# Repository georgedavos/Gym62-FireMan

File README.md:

# Gym62-FireMan
## Αυτόνομο Όχημα Ανίχνευσης Θέσης Πυρκαϊάς

Η ομάδα ρομποτικής του 62ου Γυμνασίου Αθηνών, μελετά και κατασκευάζει ένα  αυτοκινούμενο όχημα, το οποίο έχει ως σκοπό να επιτηρεί και να προστατεύει ένα δάσος από πυρκαϊά, και παράλληλα να μεταδίδει τα δεδομένα διαμέσου WiFi σημείου πρόσβασης που διαθέτει ενσωματωμένο.

Το Gym62-FireMan βασίστηκε σε ένα ερπυστριοφόρο σκάφος εκσκαφέα, το οποίο τροποποιήθηκε κατάλληλα για τις ανάγκες του έργου, ελάχιστης αξίας, και σε έναν ειδικό αισθητήρα παράταξης υπερύθρων ακτίνων. 

## Περιγραφή πλοήγησης

 Το σύστημα βασίζεται σε ένα αισθητήρα παράταξης υπέρυθρων ακτίνων.

Ο αισθητήρας παράταξης είναι δομημένος σε ένα πίνακα 8*8 στοιχείων, δίνοντας 64 ανεξάρτητα σημεία μέτρησης της θερμότητας.
 Χωρίζοντας τον αισθητήρα σε 8 ζώνες ορίζοντα, ανιχνεύεται ο ορίζοντας στον οποίο εμφανίζεται η μέγιστη θερμότητα. Με βάση τον επιλεγμένο ορίζοντα, το όχημα μεταβάλει την ταχύτητα των ερπυστριών συνεχώς, αναλογικά σε σχέση πάντα με την θέση της μέγιστης θερμότητας στον επιλεγμένο ορίζοντα.
 Αυτή ή συνεχώς μεταβαλλόμενη ταχύτητα των ερπυστριών οδηγεί με μεγάλη ακρίβεια το όχημα στην θέση της πυρκαϊάς.   
 Πιο συγκεκριμένα το όχημα περιστρέφεται συνεχώς γύρω από τον εαυτό του μετρώντας τα θερμικά φορτία του πεδίου ορατότητας. Εάν κατά την περιστροφή, μετρηθεί θερμικό φορτίο μεγαλύτερο από το προκαθορισμένο ( Triger ), τότε σταματάει και κινείται προς αυτό, διορθώνοντάς συνεχώς την πορεία του φροντίζοντας να την διατηρεί σταθερή και ευθεία μπροστά με κέντρο πάντα το μέγιστο θερμικό φορτίο, επικοινωνώντας ταυτόχρονα με το κέντρο ελέγχου μεταδίδοντας σήματα σχετικά με τις λειτουργίες του και αποδέχεται ρυθμίσεις πλοήγησης.

## Λογισμικό Κέντρου Ελέγχου.
Το Gym62RCNT είναι μια εφαρμογή τηλεμετρίας για τον έλεγχο και της ρυθμίσεις του οχήματος.
Αναπτύσσεται σε περιβάλλον NetBeans 8.6 Java JDK 1.8.
Για να τρέξετε την εφαρμογή χωρίς την χρήση Του  NetBeans. Εγκαταστήστε το  java run time environment στο συστημά σας και τρέξτε το αρχείο  Gym62RCNT.jar

## Κύκλωμα Gym62-MM3
Πρόκειται για ένα ηλεκτρονικό κύκλωμα επέκτασης οποιασδήποτε συμβατού Arduino πού λειτουργεί ως βάση σύνδεσης όλων των περιφερειακών συστημάτων τηλεμετρίας και τηλεκήνησης.
Για την ανάπτυξη του χρησιμοποιήθηκε το Ανοιχτό λογισμικό  KiCad IDE.

## Λεπτομέρεις Περιγραφές.
Περιγραφή περιεχομένων των αρχείων και των φακέλων που έχουν ενσωματωθεί στο github βρίσκεται σε αρχείο με όνομα "GYM62-FIREMAN-TreeOfFiles-Description" στον ίδιο κατάλογο με το παρόν ( https://github.com/georgedavos/Gym62-FireMan/blob/master/GYM62-FIREMAN-TreeOfFiles-Description.odt ).

Δείτε το βίντεο του έργου στο κανάλι youtube του σχολείου μας (62ο Γυμνάσιο Αθήνας)

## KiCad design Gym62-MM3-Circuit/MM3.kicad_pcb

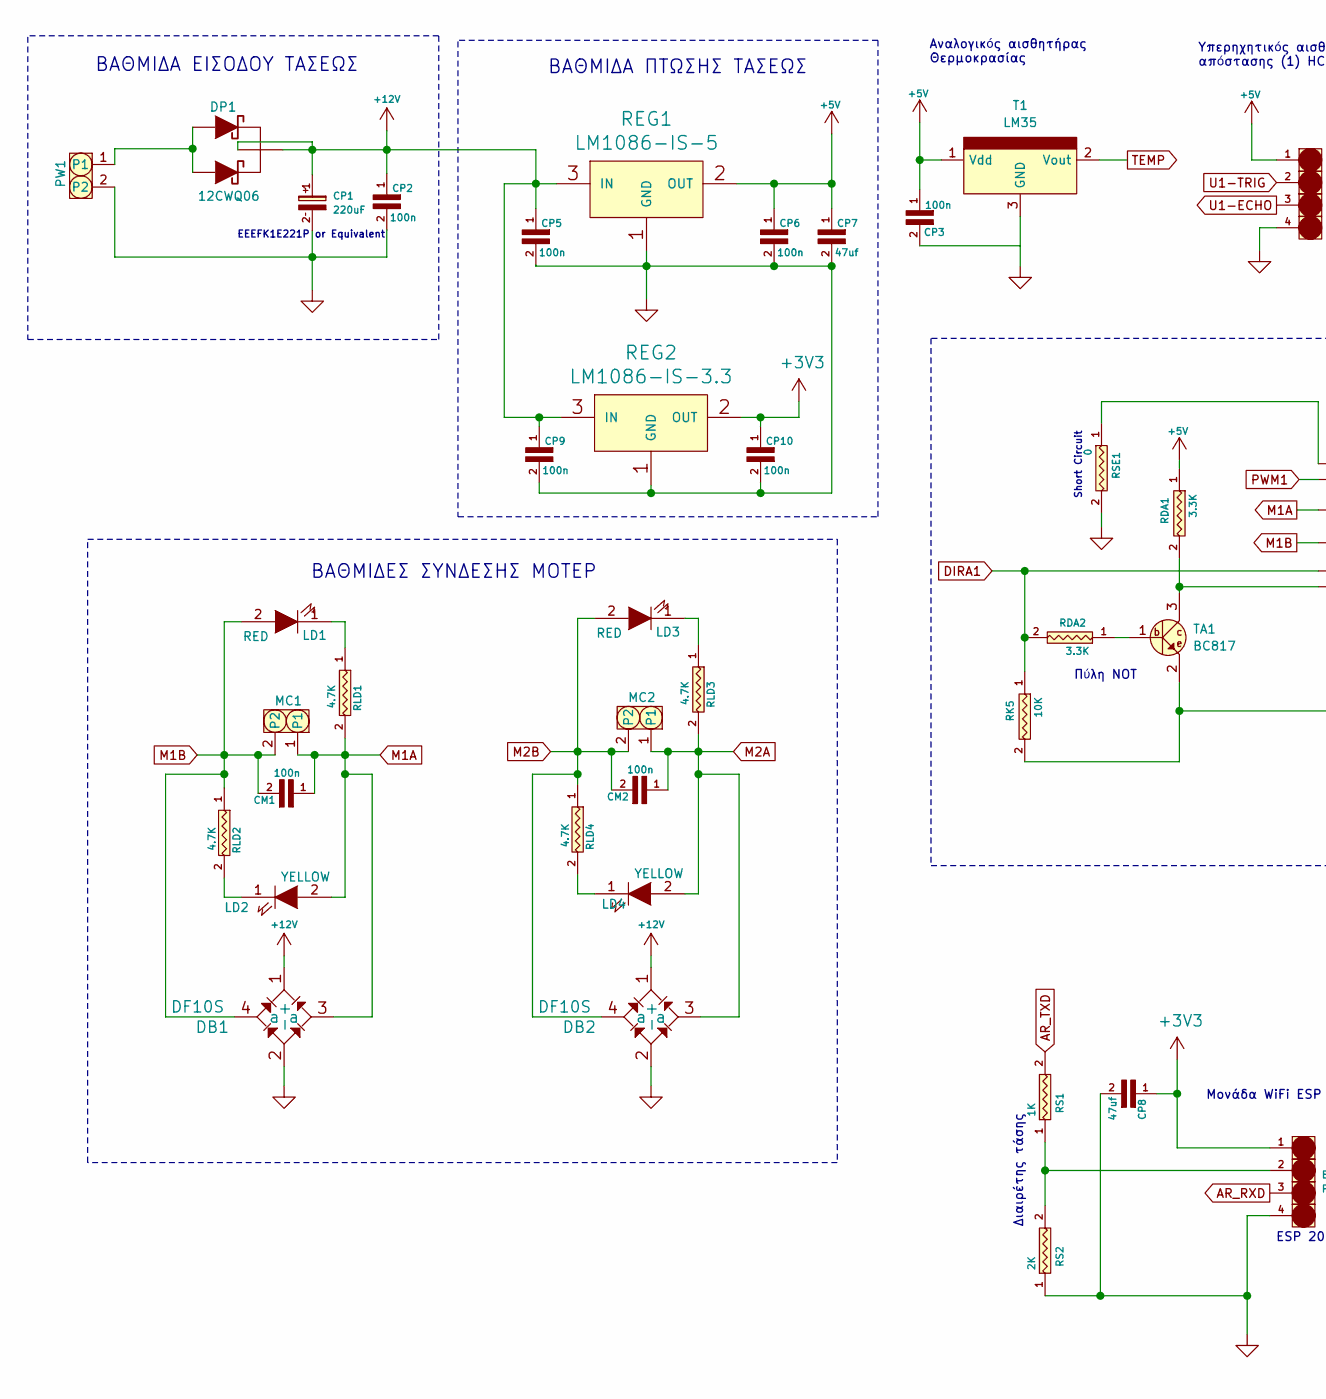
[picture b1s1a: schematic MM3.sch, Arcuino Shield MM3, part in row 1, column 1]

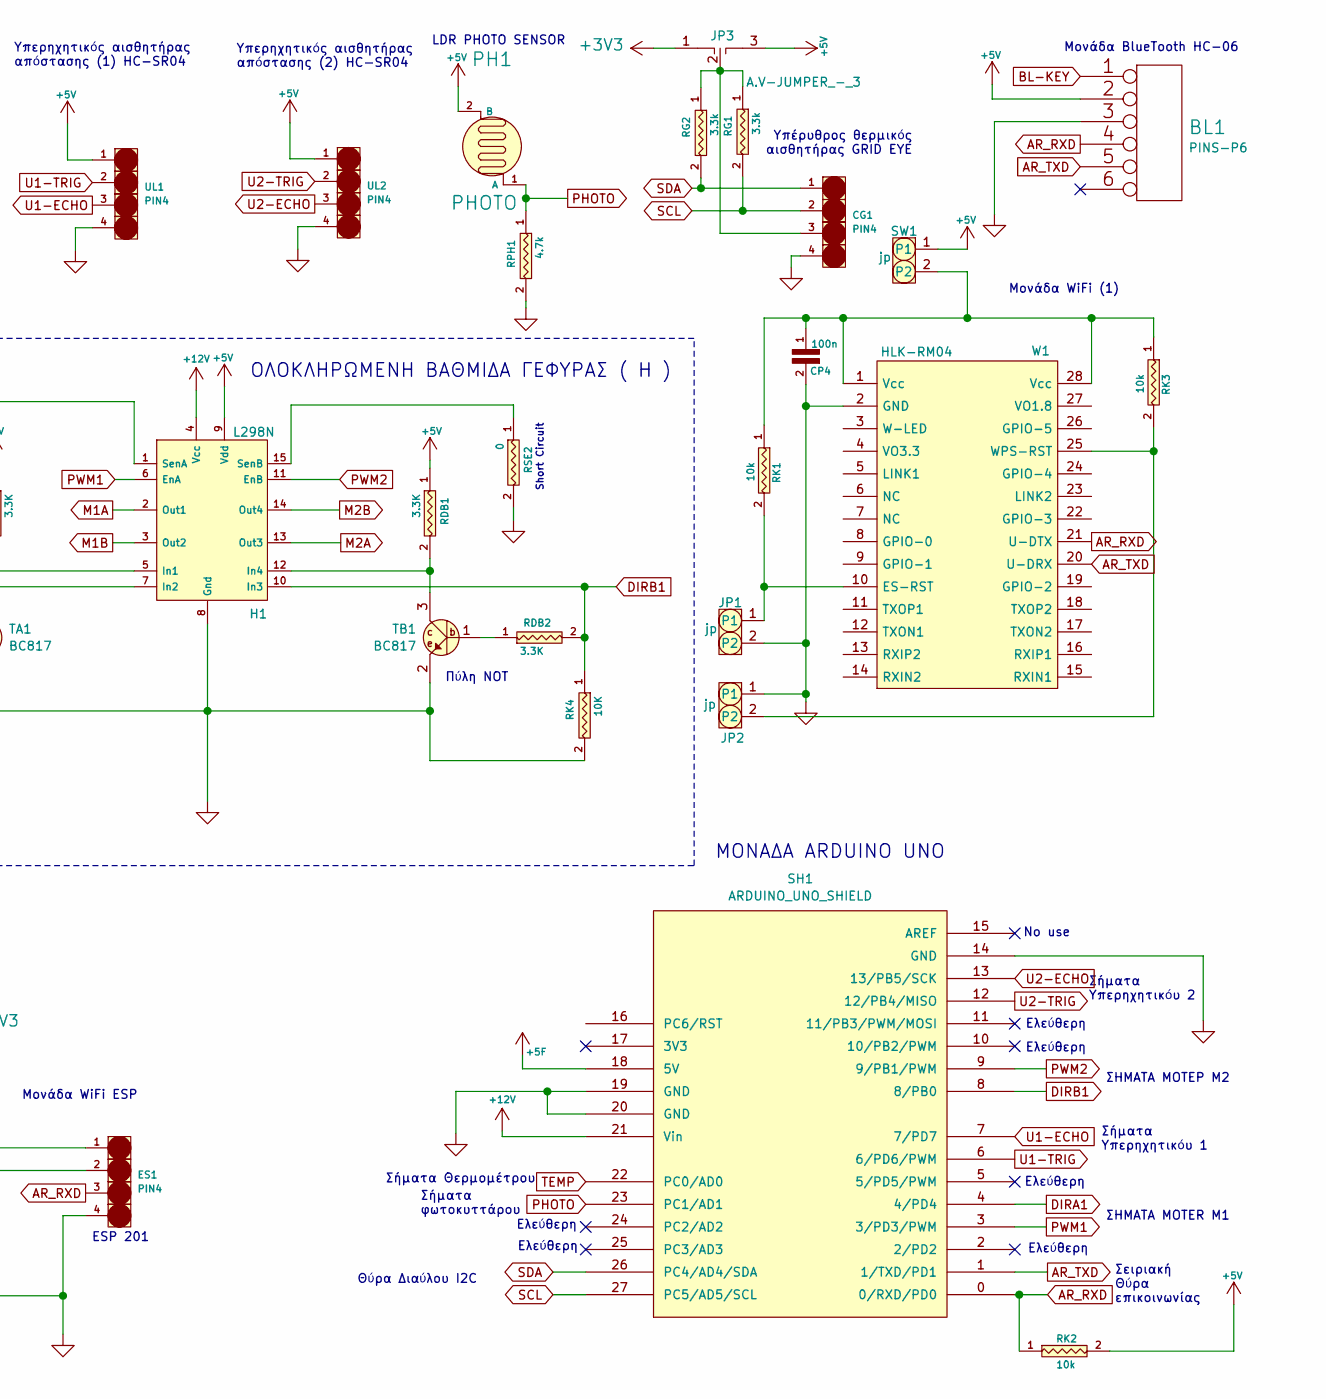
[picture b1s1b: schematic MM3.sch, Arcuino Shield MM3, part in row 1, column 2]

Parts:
BL1: PINS-P6; AV.STR-PIN-6x1
CG1: PIN4; AV.STR-MAS-4x1
CM1, CM2: 100n; AV0805
CP1: 220uF; CAP-SMD-10
CP2, CP3, CP4, CP5, CP6, CP9, CP10: 100n; AV0805
CP7, CP8: 47uf; AV1206
DB1, DB2: DF10S; Bridge-SMD
DP1: 12CWQ06; AV-D2PACK
ES1: PIN4; AV.STR-MAS-4x1
H1: L298N; Multiwat15V
JP1, JP2: jp; AV.STR-PIN-2x1
JP3: A.V-JUMPER_-_3; JP-3-MICRO
LD1, LD3: RED; PLCC2
LD2, LD4: YELLOW; PLCC2
MC1, MC2: CLEM-2P; AV.STR-MAS-2x1
PH1: PHOTO; AV.STR-MAS-2x1
PW1: CLEM-2P; AV.STR-MAS-2x1
RDA1, RDA2: 3.3K; AV1206
RDB1, RDB2: 3.3K; AV1206
REG1: LM1086-IS-5; DPAK3
REG2: LM1086-IS-3.3; DPAK3
RG1, RG2: 3.3k; AV1206
RK1, RK2, RK3: 10k; AV1206
RK4, RK5: 10K; AV1206
RLD1, RLD2, RLD3, RLD4: 4.7K; AV1206
RPH1: 4.7k; AV1206
RS1: 1K; AV1206
RS2: 2K; AV1206
RSE1, RSE2: 0; AV1206
SH1: ARDUINO_UNO_SHIELD
SW1: jp; AV.STR-PIN-2x1
T1: LM35; AV.STR-MAS-3x1
TA1: BC817; SOT23M
TB1: BC817; SOT23M
UL1, UL2: PIN4; AV.STR-PIN-4x1
W1: HLK-RM04

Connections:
+3V3: CP8.1, CP10.1, ES1.1, JP3.1, REG2.2 (OUT)
+5F: SH1.18 (5V)
+5V: BL1.2, CP3.1, CP6.1, CP7.1, H1.9 (Vdd), JP3.3, PH1.2 (B), RDA1.1, RDB1.1, REG1.2 (OUT), RK2.2, SW1.1, T1.1 (Vdd), UL1.1, UL2.1
+12V: CP1.1, CP2.1, CP5.1, CP9.1, DB1.1 (+), DB2.1 (+), DP1.2 (K), H1.4 (Vcc), REG1.3 (IN), REG2.3 (IN), SH1.21 (Vin); also elsewhere on the board
AR_RXD: BL1.4, ES1.3, RK2.1, SH1.0 (0/RXD/PD0), W1.21 (U-DTX)
AR_TXD: BL1.5, RS1.2, SH1.1 (1/TXD/PD1), W1.20 (U-DRX)
BL-KEY: BL1.1
DIRA1: H1.5 (In1), RDA2.2, RK5.1, SH1.4 (4/PD4)
DIRB1: H1.10 (In3), RDB2.2, RK4.1, SH1.8 (8/PB0)
GND: BL1.3, CG1.4, CP1.2, CP2.2, CP3.2, CP4.2, CP5.2, CP6.2, CP7.2, CP8.2, CP9.2, CP10.2, DB1.2 (-), DB2.2 (-), ES1.4, H1.8 (Gnd), JP1.2, JP2.1, PW1.2, REG1.1 (GND), REG2.1 (GND), RK4.2, RK5.2, RPH1.2, RS2.1, RSE1.2, RSE2.2, SH1.14 (GND), SH1.19 (GND), SH1.20 (GND), T1.3 (GND), TA1.2, TB1.2, UL1.4, UL2.4, W1.2 (GND); also elsewhere on the board
M1A: CM1.1, DB1.3 (a), H1.2 (Out1), LD2.2 (A), MC1.1, RLD1.2
M1B: CM1.2, DB1.4 (a), H1.3 (Out2), LD1.2 (A), MC1.2, RLD2.1
M2A: CM2.1, DB2.3 (a), H1.13 (Out3), LD4.2 (A), MC2.1, RLD3.2; also elsewhere on the board
M2B: CM2.2, DB2.4 (a), H1.14 (Out4), LD3.2 (A), MC2.2, RLD4.1; also elsewhere on the board
unnamed: CG1.3, JP3.2, RG1.1, RG2.1
unnamed: CP4.1, RK1.1, RK3.1, SW1.2, W1.1 (Vcc), W1.28 (Vcc)
unnamed: DP1.1 (A1), DP1.3 (A2), PW1.1
unnamed: ES1.2, RS1.1, RS2.2
unnamed: H1.1 (SenA), RSE1.1
unnamed: H1.7 (In2), RDA1.2, TA1.3
unnamed: H1.12 (In4), RDB1.2, TB1.3
unnamed: H1.15 (SenB), RSE2.1
unnamed: JP1.1, RK1.2, W1.10 (ES-RST)
unnamed: JP2.2, RK3.2, W1.25 (WPS-RST)
unnamed: LD1.1 (K), RLD1.1
unnamed: LD2.1 (K), RLD2.2
unnamed: LD3.1 (K), RLD3.1
unnamed: LD4.1 (K), RLD4.2
unnamed: RDA2.1, TA1.1
unnamed: RDB2.1, TB1.1
PHOTO: PH1.1 (A), RPH1.1, SH1.23 (PC1/AD1)
PWM1: H1.6 (EnA), SH1.3 (3/PD3/PWM)
PWM2: H1.11 (EnB), SH1.9 (9/PB1/PWM)
SCL: CG1.2, RG1.2, SH1.27 (PC5/AD5/SCL)
SDA: CG1.1, RG2.2, SH1.26 (PC4/AD4/SDA)
TEMP: SH1.22 (PC0/AD0), T1.2 (Vout)
U1-ECHO: SH1.7 (7/PD7), UL1.3
U1-TRIG: SH1.6 (6/PD6/PWM), UL1.2
U2-ECHO: SH1.13 (13/PB5/SCK), UL2.3
U2-TRIG: SH1.12 (12/PB4/MISO), UL2.2

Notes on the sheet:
ΣΗΜΑΤΑ MOTER M1
ΣΗΜΑΤΑ ΜΟΤΕΡ M2
Υπέρυθρος θερμικός αισθητήρας GRID EYE
Αναλογικός αισθητήρας Θερμοκρασίας
LDR PHOTO SENSOR
Σήματα Θερμομέτρου
Σήματα φωτοκυττάρου
Σήματα Υπερηχητικόυ 1
Υπερηχητικός αισθητήρας απόστασης (1) HC-SR04
Υπερηχητικός αισθητήρας απόστασης (2) HC-SR04
Σήματα Υπερηχητικόυ 2
Μονάδα WiFi (1)
Μονάδα BlueTooth HC-06
ESP 201
ΒΑΘΜΙΔΑ ΕΙΣΟΔΟΥ ΤΑΣΕΩΣ
ΒΑΘΜΙΔΑ ΠΤΩΣΗΣ ΤΑΣΕΩΣ
ΒΑΘΜΙΔΕΣ ΣΥΝΔΕΣΗΣ ΜΟΤΕΡ
ΟΛΟΚΛΗΡΩΜΕΝΗ ΒΑΘΜΙΔA ΓΕΦΥΡΑΣ ( H )
ΜΟΝΑΔΑ ARDUINO UNO
Μονάδα WiFi ESP
Σειριακή Θύρα επικοινωνίας
Ελεύθερη
No use
Θύρα Διαύλου I2C
Πύλη NOT
Διαιρέτης τάσης
EEEFK1E221P or Equivalent
Short Circuit

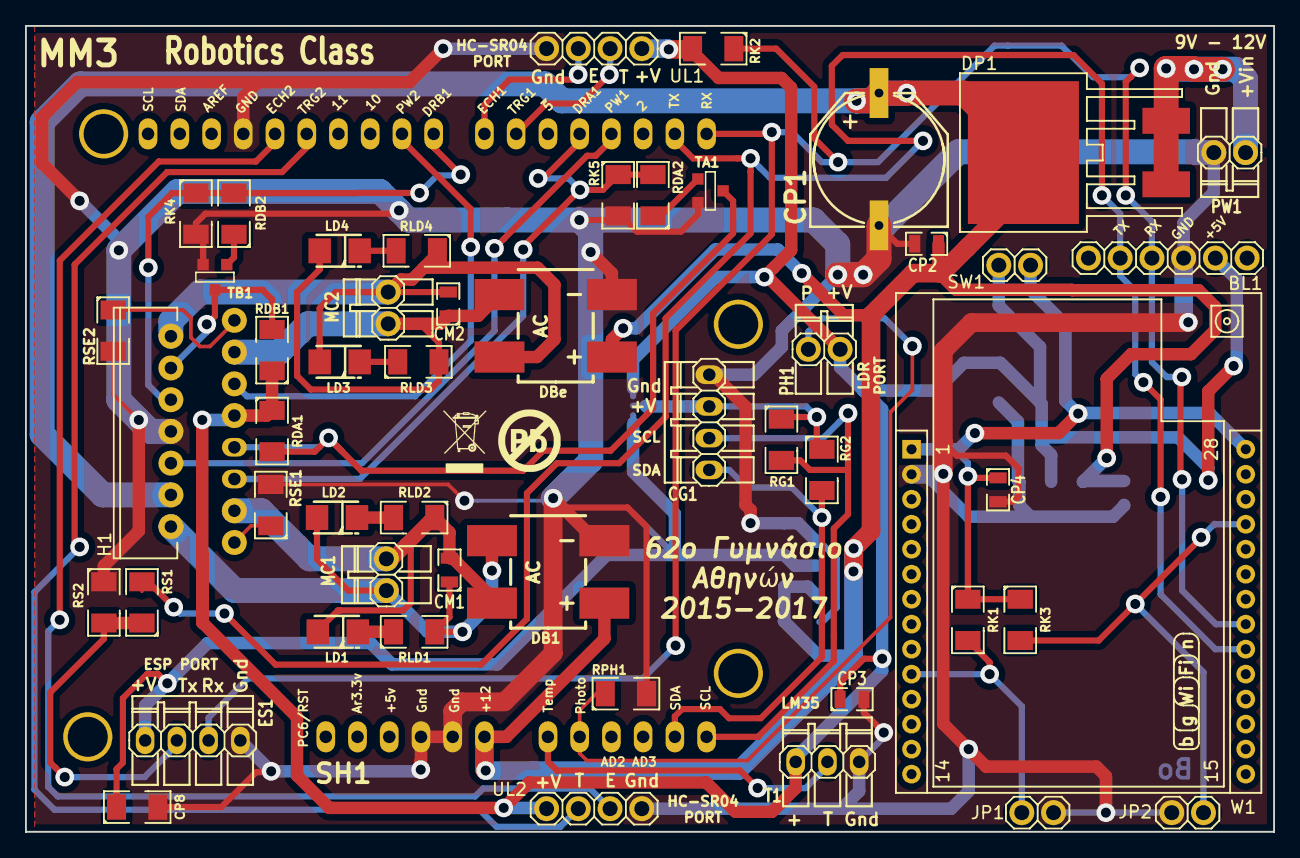
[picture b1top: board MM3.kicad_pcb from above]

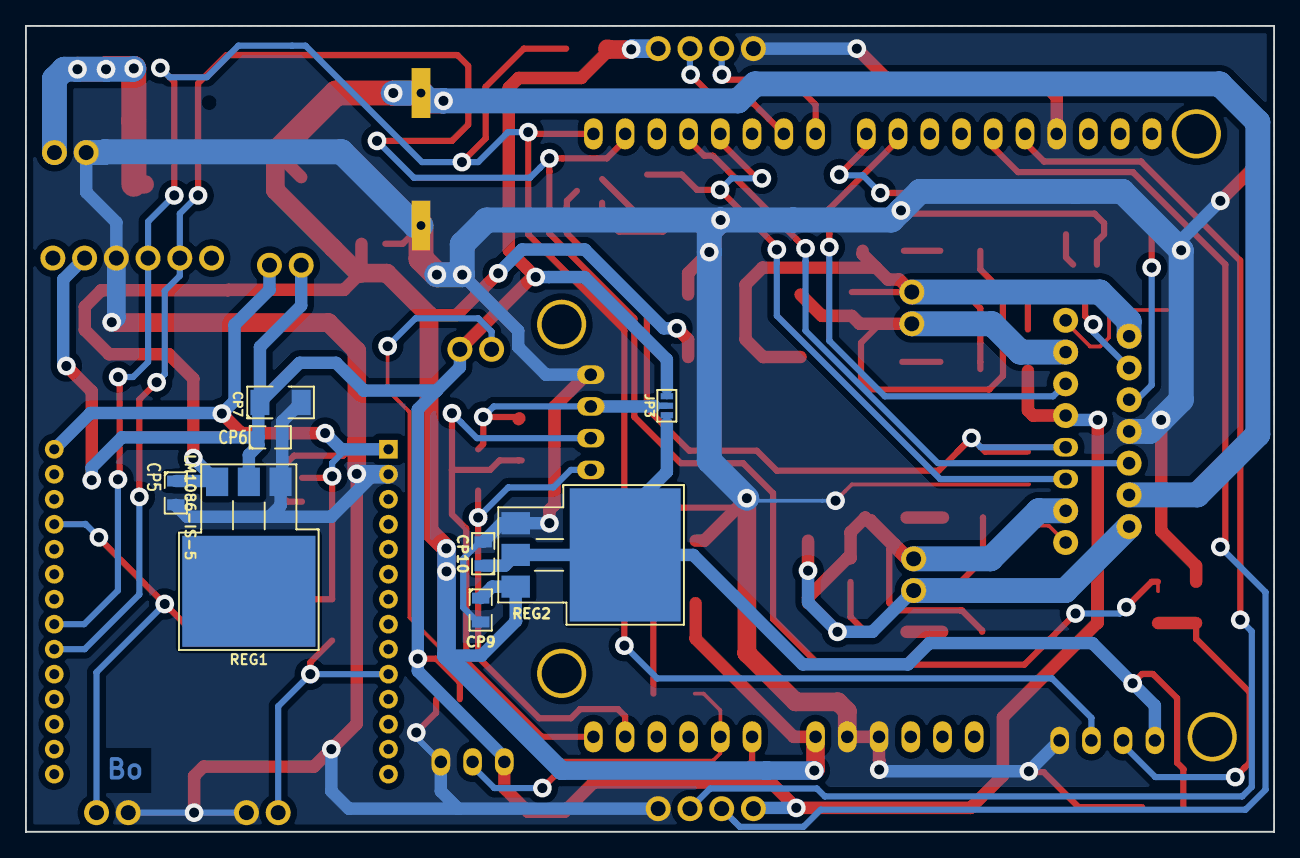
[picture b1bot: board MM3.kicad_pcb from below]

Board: 2 copper layers, 99.9 x 64.5 mm, 60 parts (8 on the bottom side), 38 nets.

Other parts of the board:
DBe: DF10S; Bridge-SMD

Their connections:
+12V: DBe.1; also elsewhere on the board
GND: DBe.2; also elsewhere on the board
M2A: DBe.3; also elsewhere on the board
M2B: DBe.4; also elsewhere on the board

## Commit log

2019-03-22 Adding Arduino Shield Gym62-MM3 Design Files
2019-03-22 Readme Additions
2019-03-22 Adding Gym62RCNT Java Aplication
2019-03-26 Add files via upload
    3D Renderings Of Gym62 MM3 Arduino Shield
2019-04-15 Adding Arduino Code and Hardware Description
2019-04-15 Rearange Images
2019-04-15 Rearange Documents
2019-04-21 Create datashets.md
    Εδώ περιλαμβάνονται τα data sheets των ηλεκτρονικών υποσυστημάτων που έχουν χρησιμοποιηθεί στο έργο 62GYM-FIREMAN
2019-04-21 Rename datashets.md to datasheets.md
2019-04-23 Add files via upload
    Additions on Descriptions and Rename File
2019-04-23 Update README.md
    Small Corrections
2019-04-24 Add files via upload
    Animated Gif
2019-05-02 Update README.md
    Link to YouTube Video
